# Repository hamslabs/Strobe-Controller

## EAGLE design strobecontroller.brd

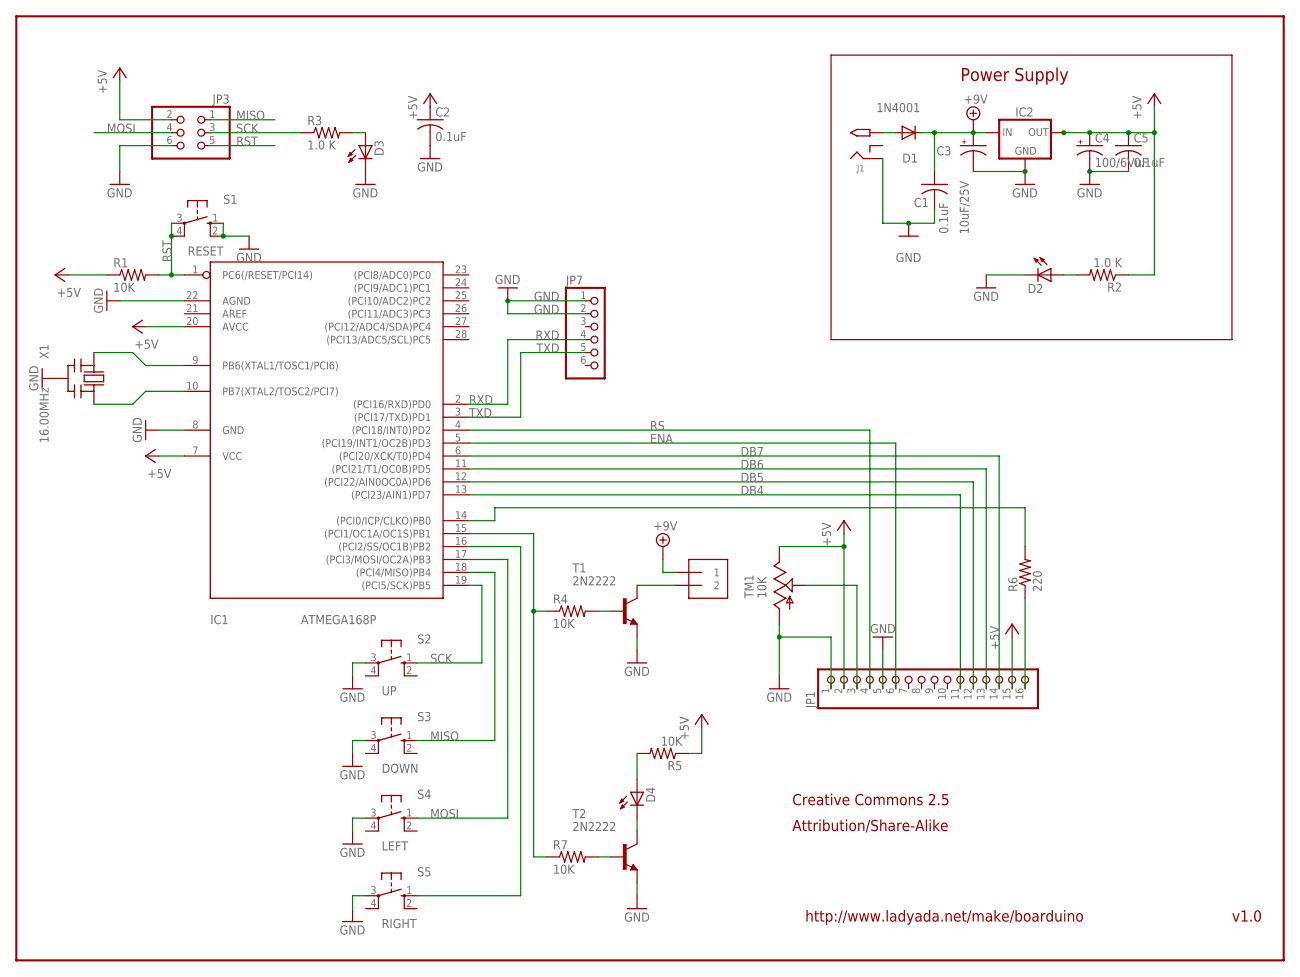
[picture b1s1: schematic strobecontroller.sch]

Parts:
C1, C2, C5: 0.1uF; C025-025X050
C3: 10uF/25V; E2,5-6
C4: 100/6VuF; E2,5-6
D1: 1N4001; DO41-10
D2, D4: Red; LED3MM
D3: Green; LED3MM
IC1: ATMEGA168P; DIL28/3
IC2: 78XXS
J1: 2.1MMJACK; PJ-102A
J2: 1X2-3.5MM
JP1: PINHD-1X16; 1X16
JP3: PINHD-2X3; 2X03
JP7: PINHD-1X6CLEAN; 1X06-CLEAN
R1, R4, R5, R7: 10K; 0207/5V
R2, R3: 1.0 K; 0207/5V
R6: 220; 0207/5V
S1: RESET; B3F-10XX
S2: UP; B3F-10XX
S3: DOWN; B3F-10XX
S4: LEFT; B3F-10XX
S5: RIGHT; B3F-10XX
T1, T2: 2N2222; TO92-EBC-OVAL
TM1: 10K; 6MM
X1: 16.00MHz; CERM_OSC

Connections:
+5V: C2.1, C4.+, C5.1, IC1.7 (VCC), IC1.20 (AVCC), IC2.OUT, JP1.2, JP1.15, JP3.2, R1.1, R2.1, R5.1, TM1.E
+9V: C1.1, C3.+, D1.C, IC2.IN, J2.1
DB4: IC1.13 ((PCI23/AIN1)PD7), JP1.11
DB5: IC1.12 ((PCI22/AIN0OC0A)PD6), JP1.12
DB6: IC1.11 ((PCI21/T1/OC0B)PD5), JP1.13
DB7: IC1.6 ((PCI20/XCK/T0)PD4), JP1.14
ENA: IC1.5 ((PCI19/INT1/OC2B)PD3), JP1.6
GND: C1.2, C2.2, C3.-, C4.-, C5.2, D2.K (C), D3.K (C), IC1.8 (GND), IC1.22 (AGND), IC2.GND, J1.RING, JP1.1, JP1.5, JP3.6, JP7.1, JP7.2, S1.1 (S), S1.2 (S1), S2.3, S3.3, S4.3, S5.3, T1.E, T2.E, TM1.A, X1.P$2 (GND)
MISO: IC1.18 ((PCI4/MISO)PB4), JP3.1, S3.1 (S)
MOSI: IC1.17 ((PCI3/MOSI/OC2A)PB3), JP3.4, S4.1 (S)
unnamed: IC1.9 (PB6(XTAL1/TOSC1/PCI6)), X1.P$1 (IN)
unnamed: IC1.10 (PB7(XTAL2/TOSC2/PCI7)), X1.P$3 (OUT)
unnamed: D2.A, R2.2
unnamed: D3.A, R3.2
unnamed: JP1.16, R6.1
unnamed: R4.2, T1.B
unnamed: J2.2, T1.C
unnamed: IC1.14 ((PCI0/ICP/CLKO)PB0), R6.2
unnamed: IC1.16 ((PCI2/SS/OC1B)PB2), S5.1 (S)
unnamed: JP1.3, TM1.S
unnamed: D4.K (C), T2.C
unnamed: D4.A, R5.2
unnamed: R7.2, T2.B
unnamed: IC1.15 ((PCI1/OC1A/OC1S)PB1), R4.1, R7.1
unnamed: D1.A, J1.TIP
RS: IC1.4 ((PCI18/INT0)PD2), JP1.4
RST: IC1.1 (PC6(/RESET/PCI14)), JP3.5, R1.2, S1.3, S1.4 (P1)
RXD: IC1.2 ((PCI16/RXD)PD0), JP7.4
SCK: IC1.19 ((PCI5/SCK)PB5), JP3.3, R3.1, S2.1 (S)
TXD: IC1.3 ((PCI17/TXD)PD1), JP7.5

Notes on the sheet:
Power Supply
v1.0
http://www.ladyada.net/make/boarduino
Creative Commons 2.5
Attribution/Share-Alike

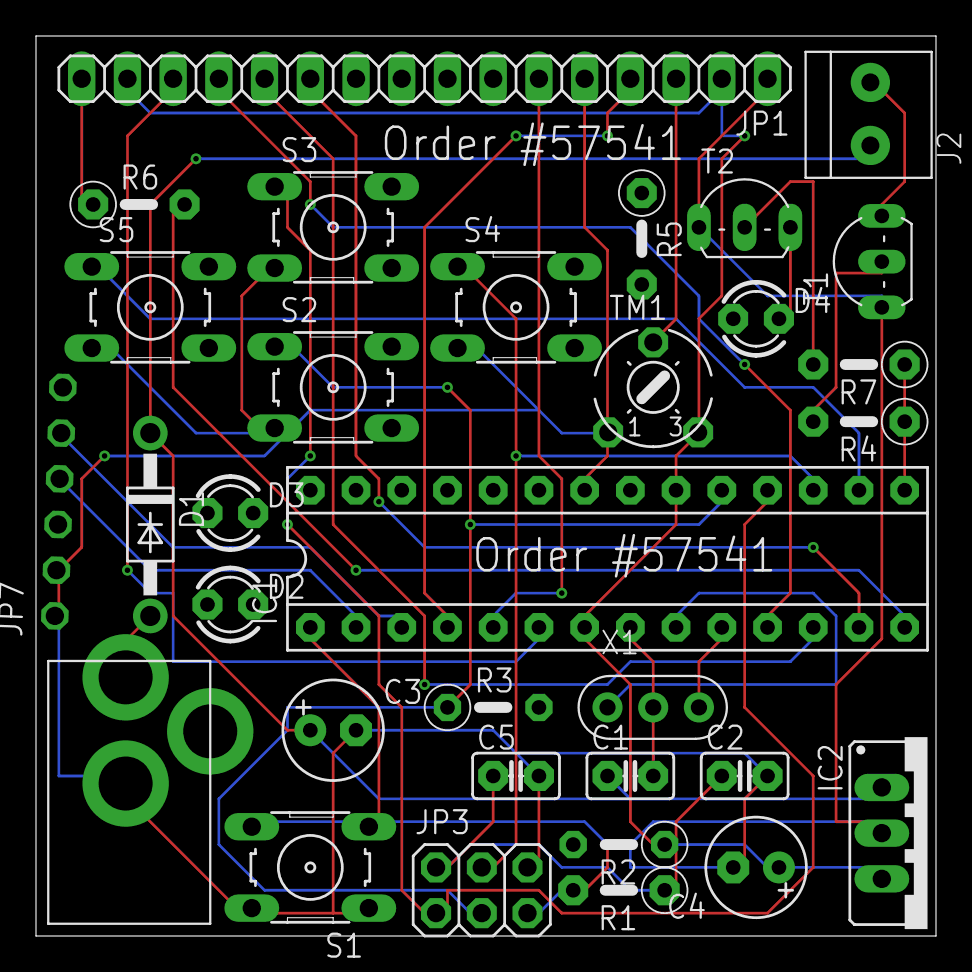
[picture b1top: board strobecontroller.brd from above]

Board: 2 copper layers, 50.0 x 50.0 mm, 32 parts (0 on the bottom side), 30 nets.

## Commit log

2012-08-22 original commit
